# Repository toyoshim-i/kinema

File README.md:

# kinema

> **Circuit Description Language & KiCad Equivalence Verification Tool**

`kinema` is an offline hardware description toolchain. It enables engineers and AI coding agents to design printed circuit boards (PCBs) by writing circuits in a **strict structural subset of Verilog**, bypassing graphical schematics entirely.

```
       Circuit Description (.v)
                 │
                 ▼
          kinema fmt & lint
                 │
                 ▼
       KiCad Netlist (.net) ──► KiCad PCB Editor (Sync)
                                       │
                                       ▼
                               Placement & Routing
                                       │
                                       ▼
  .kicad_pcb ◄──────────────► kinema check (--strict)
                               (Equiv & KiCad DRC)
```

## Philosophy

- **Code as Single Ground Truth**: Electrical connectivity originates purely in code. Graphical schematics are generated views, not authoritative models.
- **Verification Over Presumption**: Automated pad-partition equivalence and physical DRC enforce zero discrepancy between intent and layout.
- **Context-Engineering-Free**: Tooling must be self-documenting. Rather than external context stuffing, guidance and diagnostic remediations are discovered on-demand just-in-time.

## Getting Started

- **[Online Manual](https://toyoshim-i.github.io/kinema/)**: Complete architectural guides, workflows, and rule references.
- **In-CLI Guides**: Run `kinema guide` to browse the interactive documentation index, or `kinema explain <CODE>` for contextual diagnostic remediation.
- **CLI Reference**: Run `kinema --help` for available subcommands and flags.

## Installation

Pre-built binaries are available on [GitHub Releases](https://github.com/toyoshim-i/kinema/releases).

To build from source:
```bash
cargo install --path crates/kinema-cli
```

## License

MIT OR Apache-2.0

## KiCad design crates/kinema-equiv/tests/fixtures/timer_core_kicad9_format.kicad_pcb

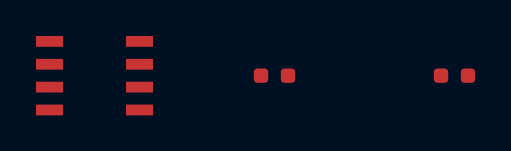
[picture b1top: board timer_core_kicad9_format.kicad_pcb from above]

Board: 2 copper layers, 3 parts (0 on the bottom side), 4 nets, no tracks yet.

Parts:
C1: 100n; C_0603_1608Metric
R1: 10k; R_0603_1608Metric
U1: NE555DR; SOIC-8_3.9x4.9mm_P1.27mm

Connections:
DIS: R1.2, U1.7
GND: C1.2, U1.1
TRIG: U1.2, U1.6
VCC: C1.1, R1.1, U1.4, U1.8

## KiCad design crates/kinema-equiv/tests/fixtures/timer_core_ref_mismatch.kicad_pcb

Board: 0 copper layers, 3 parts (0 on the bottom side), 4 nets, no tracks yet.

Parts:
C1: 100n; C_0603_1608Metric
R1: 10k; R_0603_1608Metric
U9: NE555DR; SOIC-8_3.9x4.9mm_P1.27mm

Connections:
DIS: R1.2, U9.7
GND: C1.2, U9.1
TRIG: U9.2, U9.6
VCC: C1.1, R1.1, U9.4, U9.8
